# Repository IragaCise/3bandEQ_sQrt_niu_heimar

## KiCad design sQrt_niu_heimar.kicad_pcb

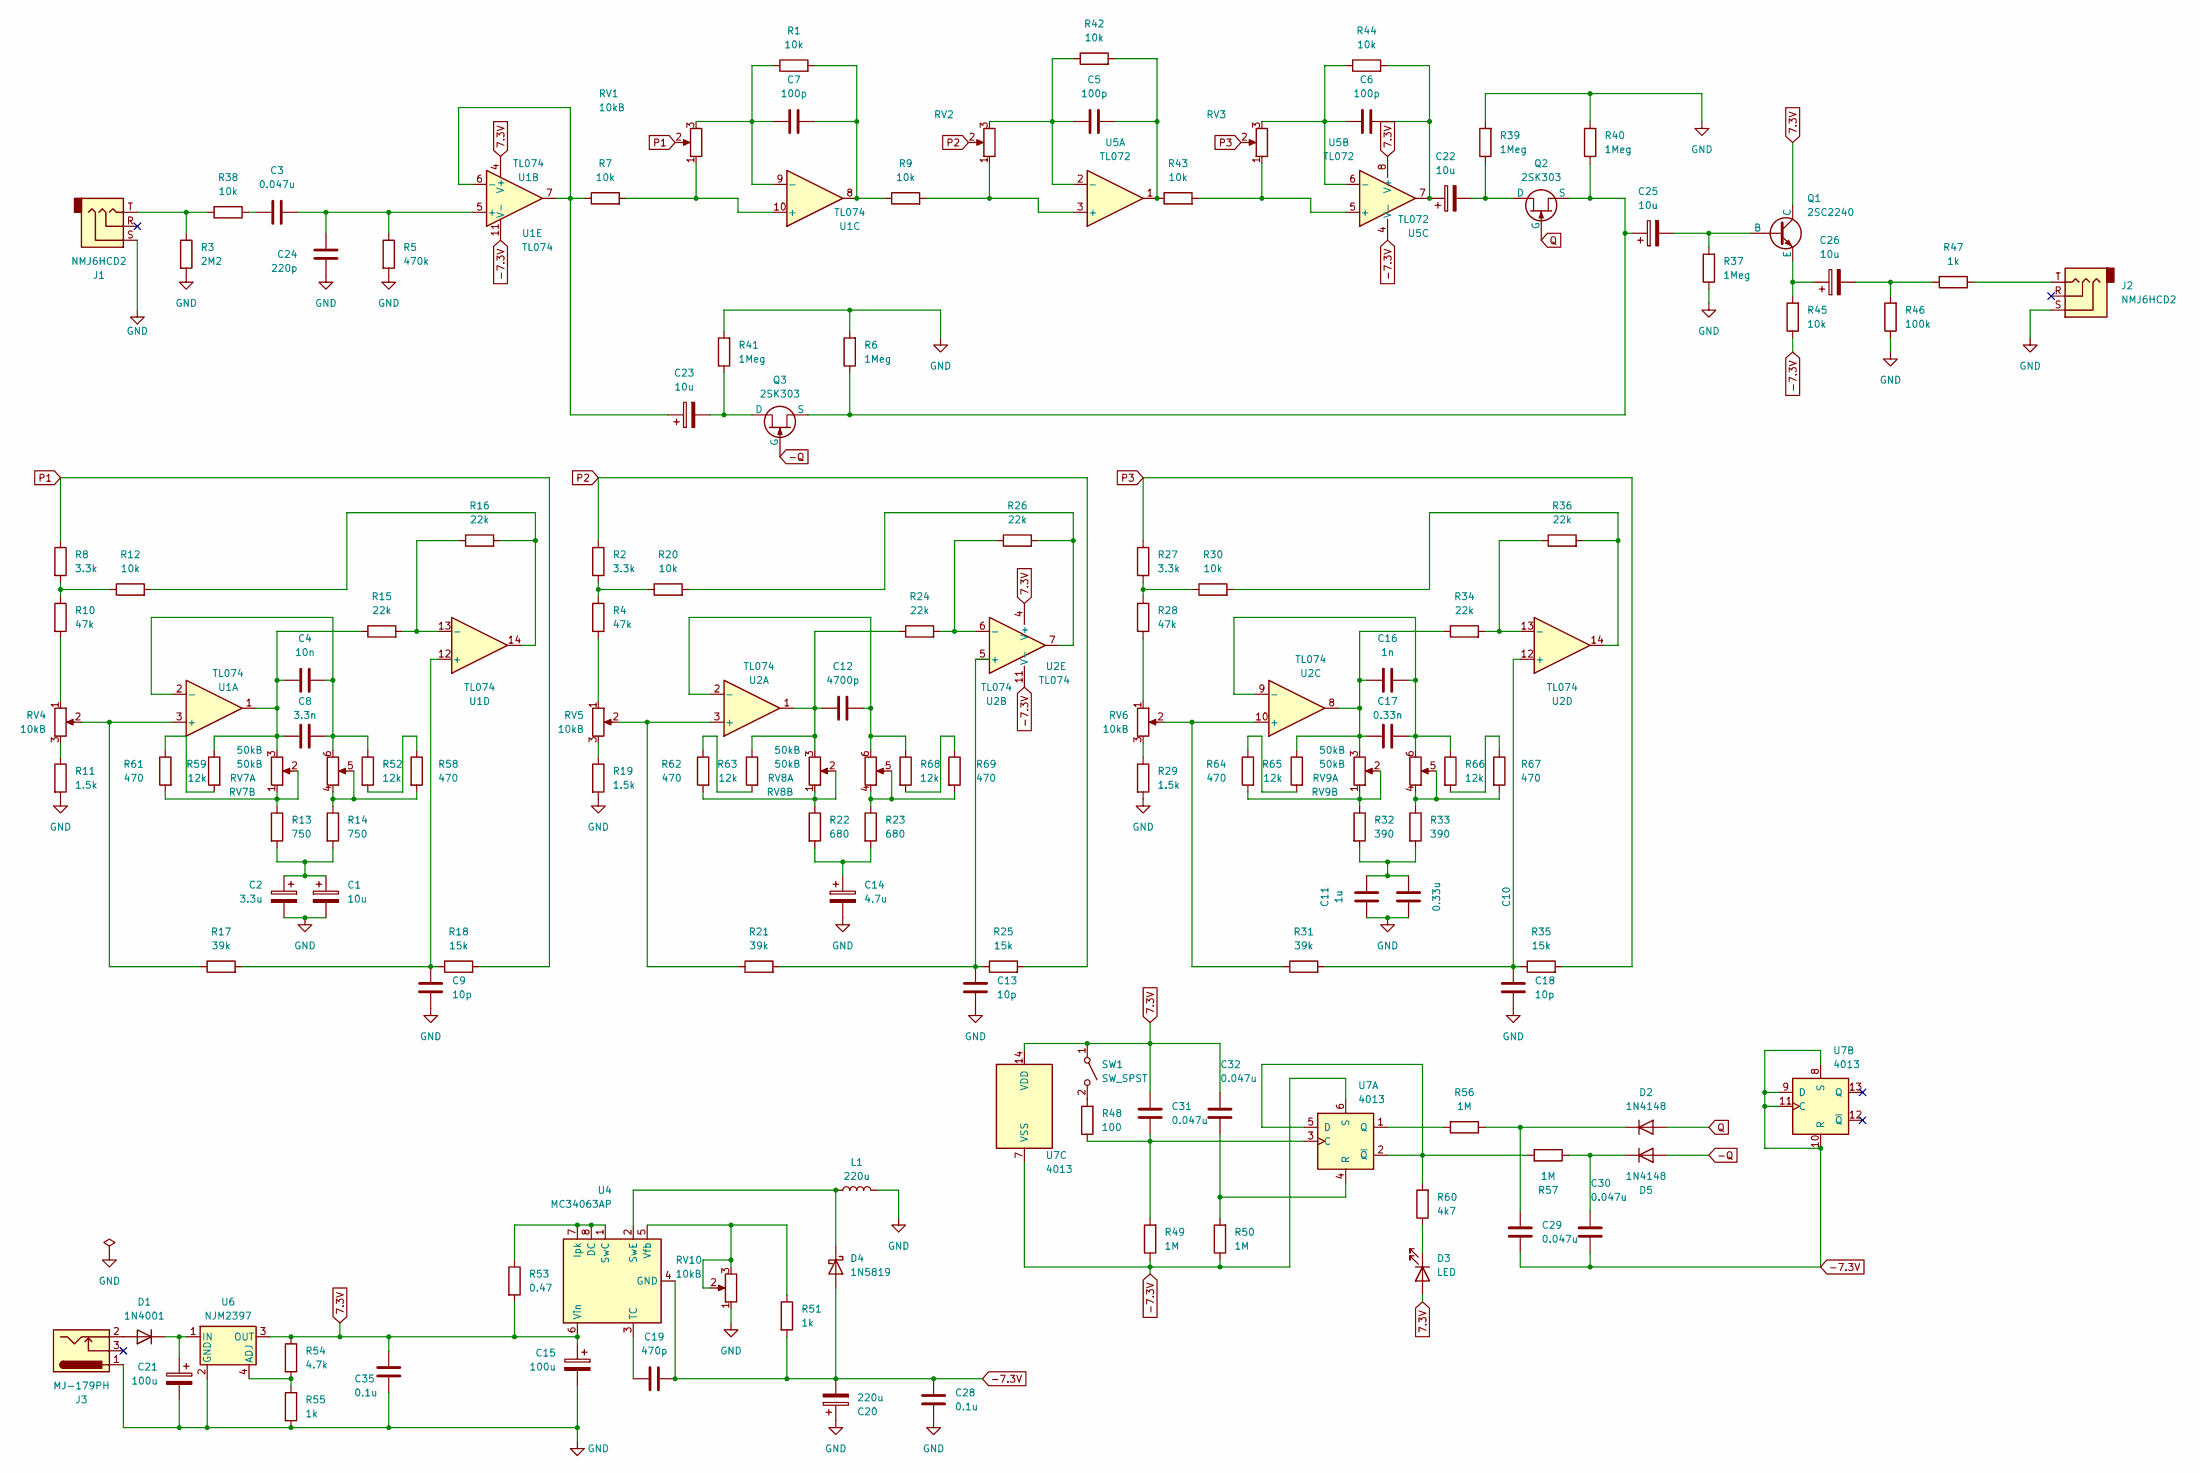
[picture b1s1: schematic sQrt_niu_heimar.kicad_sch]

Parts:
C1, C22, C23, C25, C26: 10u; CP_Radial_D5.0mm_P2.00mm
C2: 3.3u; CP_Radial_D5.0mm_P2.00mm
C3, C29, C30, C31, C32: 0.047u; C_Rect_L7.2mm_W2.5mm_P5.00mm_FKS2_FKP2_MKS2_MKP2
C4: 10n; C_Rect_L6.5mm_W3.5mm_P3.50mm_MKS02_FKP02
C5, C6, C7: 100p; C_Rect_L7.0mm_W2.5mm_P5.00mm
C8: 3.3n; C_Rect_L6.0mm_W3.0mm_P3.50mm_MKS02_FKP02
C9, C13, C18: 10p; C_Rect_L7.0mm_W2.5mm_P5.00mm
C10: 0.33u; C_Rect_L13.0mm_W8.0mm_P10.00mm_FKS3_FKP3_MKS4
C11: 1u; C_Rect_L7.2mm_W5.5mm_P5.00mm_FKS2_FKP2_MKS2_MKP2
C12: 4700p; C_Rect_L6.5mm_W3.5mm_P3.50mm_MKS02_FKP02
C14: 4.7u; CP_Radial_D5.0mm_P2.00mm
C15, C21: 100u; CP_Radial_D10.0mm_P5.00mm
C16: 1n; C_Rect_L6.5mm_W3.5mm_P3.50mm_MKS02_FKP02
C17: 0.33n; C_Rect_L6.0mm_W3.0mm_P3.50mm_MKS02_FKP02
C19: 470p; C_Rect_L7.0mm_W2.5mm_P5.00mm
C20: 220u; CP_Radial_D8.0mm_P2.50mm
C24: 220p; C_Rect_L7.0mm_W2.5mm_P5.00mm
C28, C35: 0.1u; C_Rect_L7.0mm_W2.5mm_P5.00mm
D1: 1N4001; D_DO-41_SOD81_P7.62mm_Horizontal
D2, D5: 1N4148; D_DO-35_SOD27_P7.62mm_Horizontal
D3: LED; LED_D3.0mm
D4: 1N5819; D_DO-41_SOD81_P10.16mm_Horizontal
J1, J2: NMJ6HCD2; Jack_6.35mm_Neutrik_NMJ6HCD2_Horizontal
J3: MJ-179PH; BarrelJack_Effector
L1: 220u; L_Axial_L11.0mm_D4.5mm_P5.08mm_Vertical_Fastron_MECC
Q1: 2SC2240; TO-92_Inline_4
Q2, Q3: 2SK303; TO-92_Inline_2
R1, R7, R9, R12, R20, R30, R38, R42, R43, R44, R45: 10k; R_Axial_DIN0207_L6.3mm_D2.5mm_P7.62mm_Horizontal
R2, R8, R27: 3.3k; R_Axial_DIN0207_L6.3mm_D2.5mm_P7.62mm_Horizontal
R3: 2M2; R_Axial_DIN0207_L6.3mm_D2.5mm_P7.62mm_Horizontal
R4, R10, R28: 47k; R_Axial_DIN0207_L6.3mm_D2.5mm_P7.62mm_Horizontal
R5: 470k; R_Axial_DIN0207_L6.3mm_D2.5mm_P7.62mm_Horizontal
R6, R37, R39, R40, R41: 1Meg; R_Axial_DIN0207_L6.3mm_D2.5mm_P7.62mm_Horizontal
R11, R19, R29: 1.5k; R_Axial_DIN0207_L6.3mm_D2.5mm_P7.62mm_Horizontal
R13, R14: 750; R_Axial_DIN0207_L6.3mm_D2.5mm_P7.62mm_Horizontal
R15, R16, R24, R26, R34, R36: 22k; R_Axial_DIN0207_L6.3mm_D2.5mm_P7.62mm_Horizontal
R17, R21, R31: 39k; R_Axial_DIN0207_L6.3mm_D2.5mm_P7.62mm_Horizontal
R18, R25, R35: 15k; R_Axial_DIN0207_L6.3mm_D2.5mm_P7.62mm_Horizontal
R22, R23: 680; R_Axial_DIN0207_L6.3mm_D2.5mm_P7.62mm_Horizontal
R32, R33: 390; R_Axial_DIN0207_L6.3mm_D2.5mm_P7.62mm_Horizontal
R46: 100k; R_Axial_DIN0207_L6.3mm_D2.5mm_P7.62mm_Horizontal
R47, R51, R55: 1k; R_Axial_DIN0207_L6.3mm_D2.5mm_P7.62mm_Horizontal
R48: 100; R_Axial_DIN0207_L6.3mm_D2.5mm_P7.62mm_Horizontal
R49, R50, R56, R57: 1M; R_Axial_DIN0207_L6.3mm_D2.5mm_P7.62mm_Horizontal
R52, R59, R63, R65, R66, R68: 12k; R_Axial_DIN0207_L6.3mm_D2.5mm_P7.62mm_Horizontal
R53: 0.47; R_Axial_DIN0207_L6.3mm_D2.5mm_P7.62mm_Horizontal
R54: 4.7k; R_Axial_DIN0207_L6.3mm_D2.5mm_P7.62mm_Horizontal
R58, R61, R62, R64, R67, R69: 470; R_Axial_DIN0207_L6.3mm_D2.5mm_P7.62mm_Horizontal
R60: 4k7; R_Axial_DIN0207_L6.3mm_D2.5mm_P2.54mm_Vertical
RV1, RV2, RV3, RV4, RV5, RV6: 10kB; Potentiometer_Alps_RK09K_Single_Vertical
RV7, RV8, RV9: 50kB; Potentiometer_Alps_RK12L12C_Double_Vertical
RV10: 10kB; Potentiometer_Trimmer
SW1: SW_SPST; MountingHole_2.2mm_M2_Pad_Double_2
U1, U2: TL074; DIP-14_W7.62mm_Socket_LongPads
U4: MC34063AP; DIP-8_W7.62mm
U5: TL072; DIP-8_W7.62mm
U6: NJM2397; TO-220-4_Vertical_NJM2397
U7: 4013; DIP-14_W7.62mm

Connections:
7.3V: C15.1, C31.2, C32.2, C35.1, D3.2 (A), Q1.1 (C), R53.2, R54.1, SW1.1 (A), U1.4 (V+), U2.4 (V+), U4.6 (Vin), U5.8 (V+), U6.3 (OUT), U7.14 (VDD)
-7.3V: C19.2, C20.2, C28.1, C29.1, C30.1, D4.2 (A), R45.1, R49.1, R50.1, R51.2, U1.11 (V-), U2.11 (V-), U4.4 (GND), U5.4 (V-), U7.6 (S), U7.7 (VSS), U7.8 (S), U7.9 (D), U7.10 (R), U7.11 (C)
-Q: D5.2 (A), Q3.2 (G)
GND: C1.2, C2.2, C9.2, C10.2, C11.2, C13.2, C14.2, C15.2, C18.2, C20.1, C21.2, C24.1, C28.2, C35.2, J1.S, J2.S, J3.1, L1.2, R3.2, R5.2, R6.2, R11.2, R19.2, R29.2, R37.1, R39.2, R40.2, R41.2, R46.1, R55.2, RV10.1, U6.2 (GND)
unnamed: C1.1, C2.1, R13.2, R14.2
unnamed: C3.1, R38.1
unnamed: C4.1, C8.1, R15.1, R59.1, RV7.3, U1.1
unnamed: C5.2, R42.2, R43.1, U5.1
unnamed: C7.2, R1.2, R9.1, U1.8
unnamed: C10.1, C11.1, R32.2, R33.2
unnamed: C12.1, R24.1, R63.1, RV8.3, U2.1
unnamed: C14.1, R22.2, R23.2
unnamed: C16.1, C17.1, R34.1, R65.1, RV9.3, U2.8
unnamed: C6.2, C22.1, R44.2, U5.7
unnamed: C26.2, R46.2, R47.2
unnamed: D1.2 (A), J3.2
unnamed: C21.1, D1.1 (K), U6.1 (IN)
unnamed: C29.2, D2.1 (K), R56.1
unnamed: D3.1 (K), R60.1
unnamed: D4.1 (K), L1.1, U4.2 (SwE)
unnamed: C30.2, D5.1 (K), R57.1
unnamed: J1.T, R3.1, R38.2
unnamed: J2.T, R47.1
unnamed: C25.2, Q1.2 (B), R37.2
unnamed: C26.1, Q1.3 (E), R45.2
unnamed: C22.2, Q2.1 (D), R39.1
unnamed: C25.1, Q2.3 (S), Q3.3 (S), R6.1, R40.1
unnamed: C23.2, Q3.1 (D), R41.1
unnamed: R2.2, R4.1, R20.1
unnamed: R4.2, RV5.1
unnamed: R8.2, R10.1, R12.1
unnamed: R10.2, RV4.1
unnamed: R11.1, RV4.3
unnamed: R12.2, R16.2, U1.14
unnamed: R13.1, R61.2, RV7.1, RV7.2
unnamed: R14.1, R58.2, RV7.4, RV7.5
unnamed: R19.1, RV5.3
unnamed: R20.2, R26.2, U2.7
unnamed: R22.1, R62.2, RV8.1, RV8.2
unnamed: R23.1, R69.2, RV8.4, RV8.5
unnamed: R27.2, R28.1, R30.1
unnamed: R28.2, RV6.1
unnamed: R29.1, RV6.3
unnamed: R30.2, R36.2, U2.14
unnamed: R32.1, R64.2, RV9.1, RV9.2
unnamed: R33.1, R67.2, RV9.4, RV9.5
unnamed: R52.2, R58.1
unnamed: R59.2, R61.1
unnamed: R62.1, R63.2
unnamed: R64.1, R65.2
unnamed: R66.2, R67.1
unnamed: R68.2, R69.1
unnamed: R48.2, SW1.2 (B)
unnamed: R17.1, RV4.2, U1.3 (+)
unnamed: C4.2, C8.2, R52.1, RV7.6, U1.2 (-)
unnamed: C3.2, C24.2, R5.1, U1.5 (+)
unnamed: C23.1, R7.1, U1.6 (-), U1.7
unnamed: R7.2, RV1.1, U1.10 (+)
unnamed: C7.1, R1.1, RV1.3, U1.9 (-)
unnamed: C9.1, R17.2, R18.1, U1.12 (+)
unnamed: R15.2, R16.1, U1.13 (-)
unnamed: R21.1, RV5.2, U2.3 (+)
unnamed: C12.2, R68.1, RV8.6, U2.2 (-)
unnamed: C13.1, R21.2, R25.1, U2.5 (+)
unnamed: R24.2, R26.1, U2.6 (-)
unnamed: R31.1, RV6.2, U2.10 (+)
unnamed: C16.2, C17.2, R66.1, RV9.6, U2.9 (-)
unnamed: C18.1, R31.2, R35.1, U2.12 (+)
unnamed: R34.2, R36.1, U2.13 (-)
unnamed: R53.1, U4.1 (SwC), U4.7 (Ipk), U4.8 (DC)
unnamed: C19.1, U4.3 (TC)
unnamed: R51.1, RV10.2, RV10.3, U4.5 (Vfb)
unnamed: R9.2, RV2.1, U5.3 (+)
unnamed: C5.1, R42.1, RV2.3, U5.2 (-)
unnamed: R43.2, RV3.1, U5.5 (+)
unnamed: C6.1, R44.1, RV3.3, U5.6 (-)
unnamed: R54.2, R55.1, U6.4 (ADJ)
unnamed: C31.1, R48.1, R49.2, U7.3 (C)
unnamed: R57.2, R60.2, U7.2 (~Q), U7.5 (D)
unnamed: R56.2, U7.1 (Q)
unnamed: C32.1, R50.2, U7.4 (R)
P1: R8.1, R18.2, RV1.2
P2: R2.1, R25.2, RV2.2
P3: R27.1, R35.2, RV3.2
Q: D2.2 (A), Q2.2 (G)

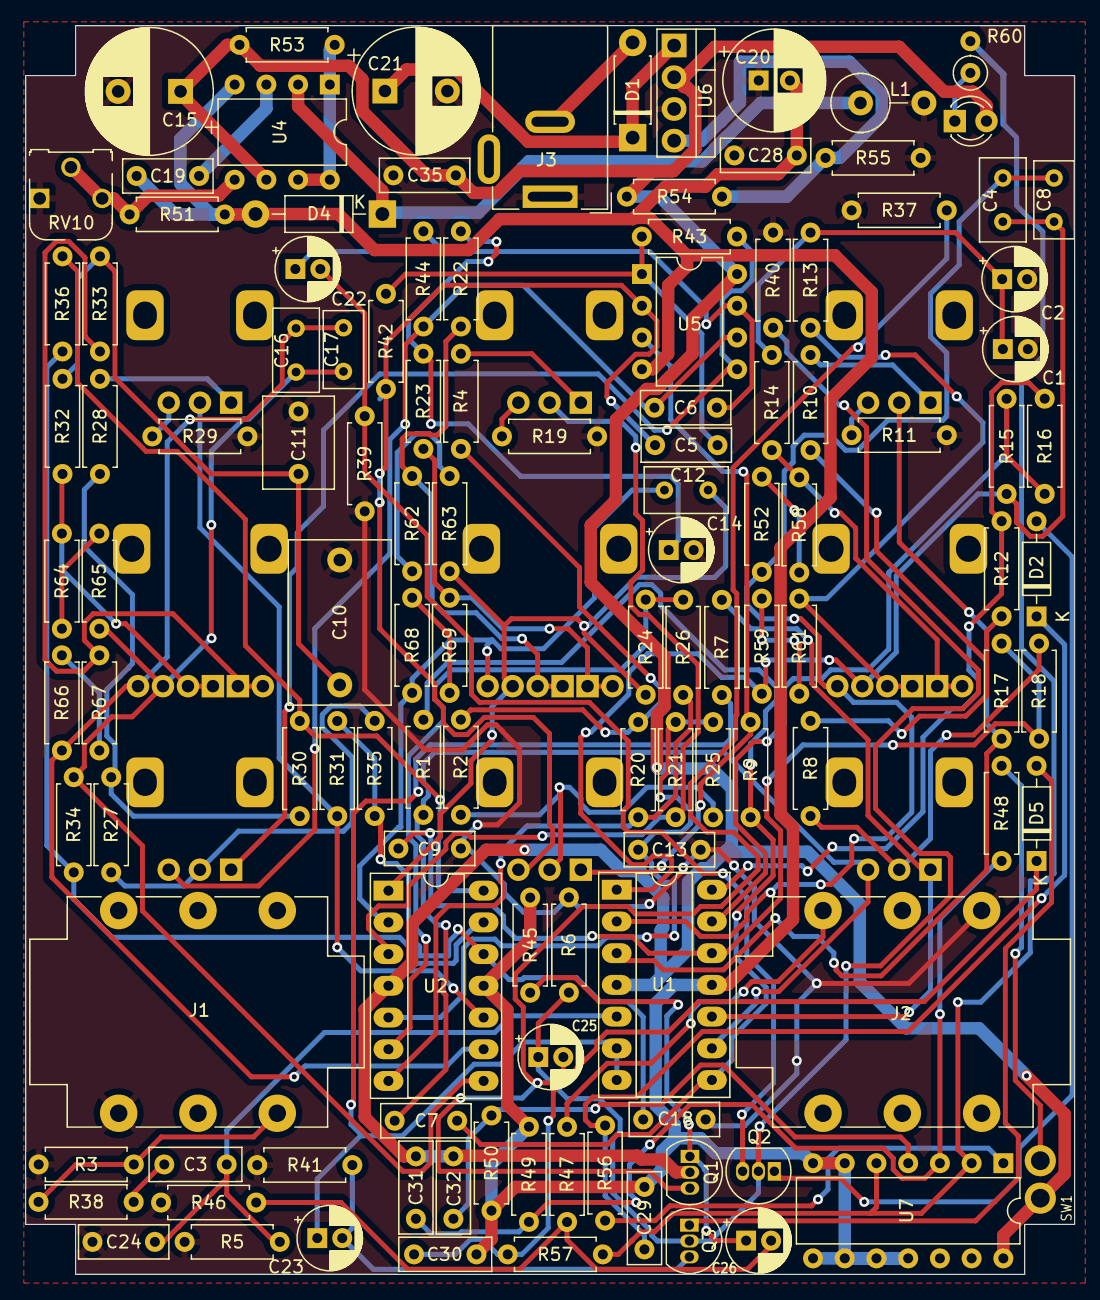
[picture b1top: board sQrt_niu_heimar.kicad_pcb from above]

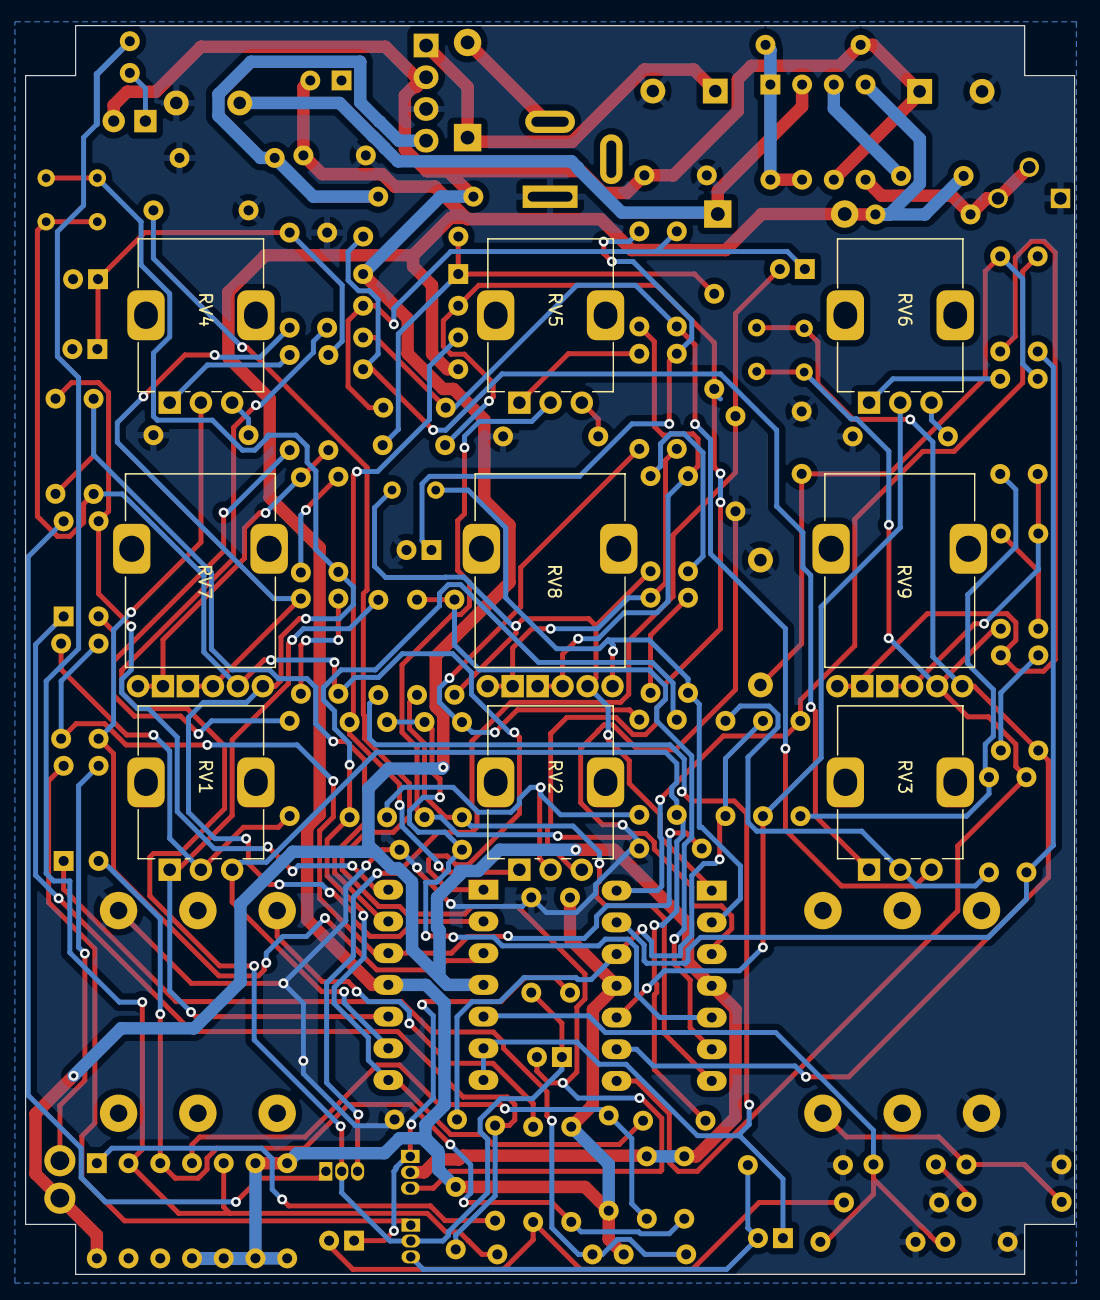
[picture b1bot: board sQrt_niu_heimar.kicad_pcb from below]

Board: 2 copper layers, 84.0 x 100.0 mm, 130 parts (9 on the bottom side), 85 nets.

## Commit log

2025-10-19 v1.0.0
2025-10-19 v1.0.1_test
2025-12-18 v2.0.0
